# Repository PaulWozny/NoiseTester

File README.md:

## Noise tester for voltage regulators

Borad and software required for tester of noise in power supplies.

This project created to show to show progress in my engineering thesis:

- PL: "Celem pracy jest opracowanie i zbudowanie niskoszumnego układu pozwalającego na pomiar szumów własnych liniowych stabilizatorów napięcia w paśmie do 1 MHz."
- EN: "The goal is to create low noise device which will allow mesure noise of the linear regulatores up to 1MHz"

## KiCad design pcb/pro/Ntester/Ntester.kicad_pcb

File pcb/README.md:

# NoiseTester
Borad and software required for tester of noise in power supplies.

This project created to show to show progress in my engineering thesis:

- PL: "Celem pracy jest opracowanie i zbudowanie niskoszumnego układu pozwalającego na pomiar szumów własnych liniowych stabilizatorów napięcia w paśmie do 1 MHz."
- EN: "The goal is to create low noise device which will allow mesure noise of the linear regulatores up to 1MHz"

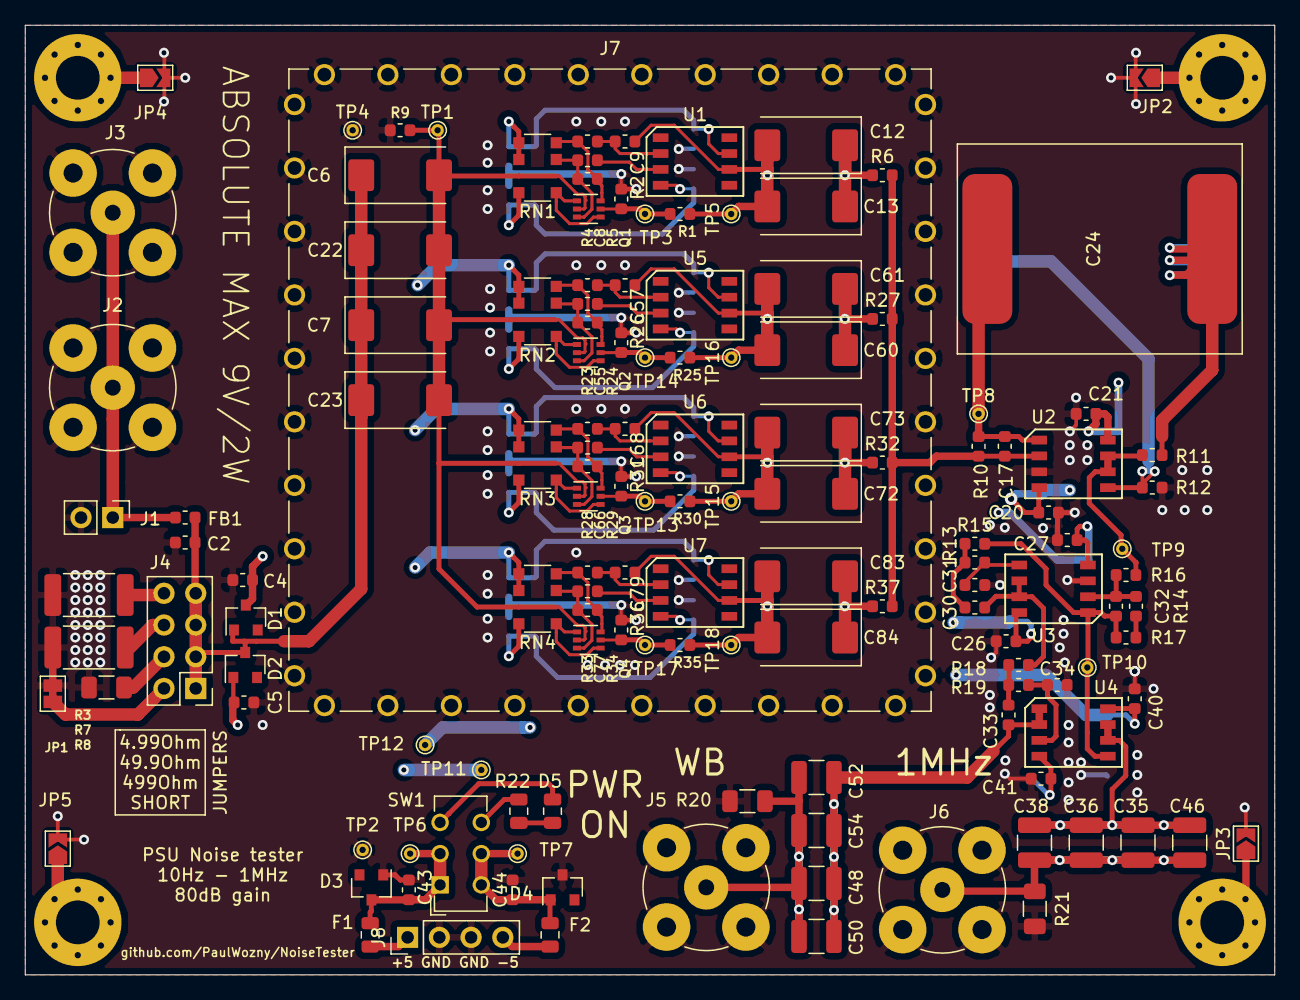
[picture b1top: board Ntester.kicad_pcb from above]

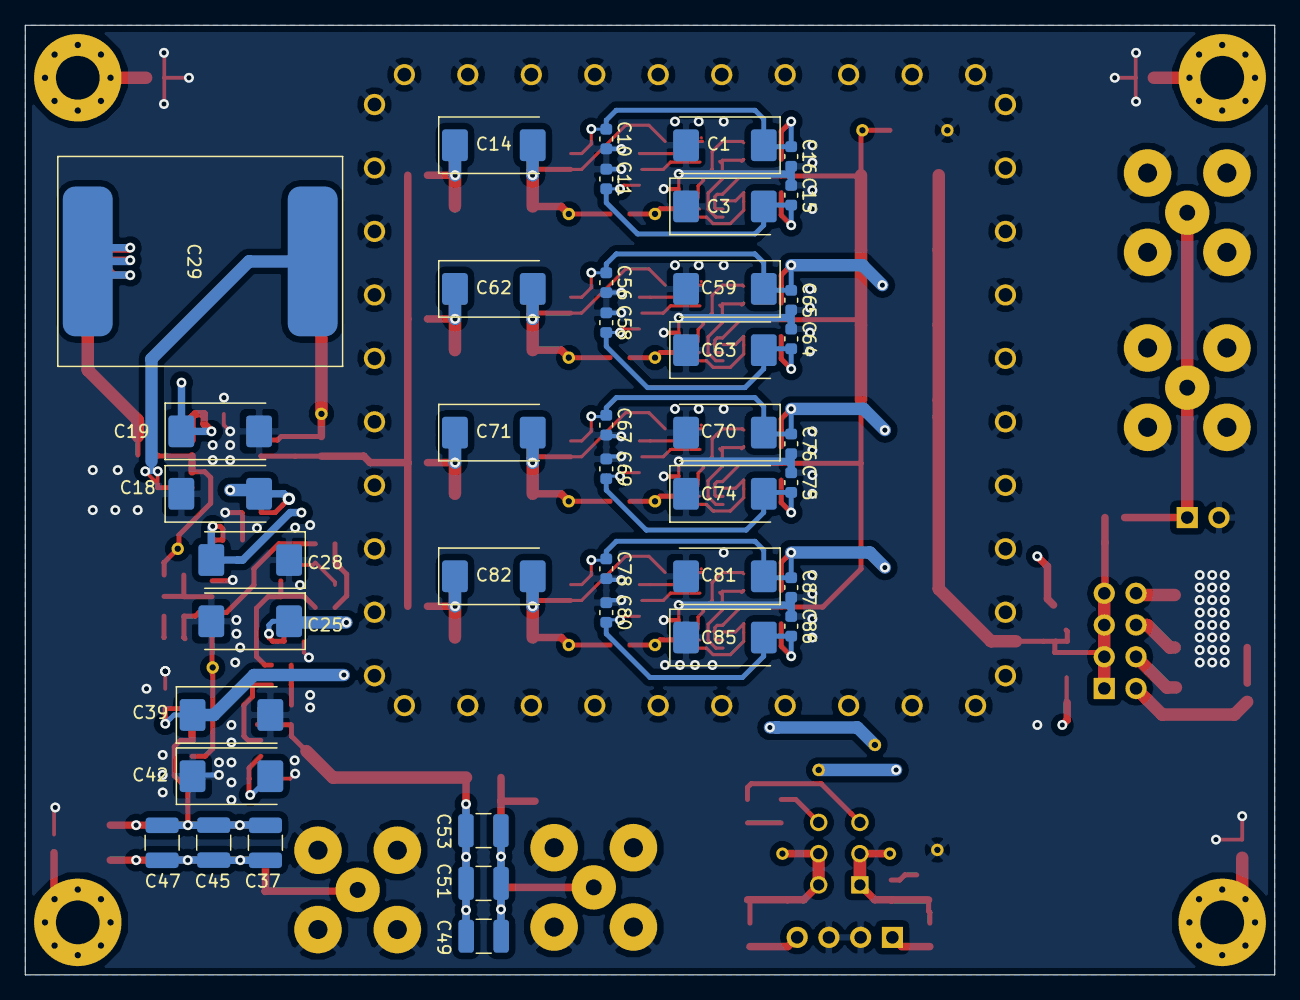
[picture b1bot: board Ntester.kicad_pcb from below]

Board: 4 copper layers, 100.0 x 76.0 mm, 183 parts (41 on the bottom side), 68 nets.

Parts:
C1, C3, C6, C7, C12, C13, C18, C19, C22, C25, C28, C39, C42, C59, C61, C62, C63, C70, C72, C73, C74, C81, C83, C84, C85: B45196-H2227-M409; CP_EIA-7343-31_Kemet-D
C2, C9, C43, C44, C57, C68, C79: 885012006007; R_0603_1608Metric
C4, C5, C10, C11, C15, C16, C20, C21, C26, C27, C40, C41, C56, C58, C64, C65, C67, C69, C75, C76, C78, C80, C86, C87: 0603B104M500CT; R_0603_1608Metric
C8, C55, C66, C77: 885012006038; R_0603_1608Metric
C14, C23, C60, C71, C82: DNP; CP_EIA-7343-31_Kemet-D
C17, C32: DNP; C_0603_1608Metric
C24, C29: SMDTD04470YA00MT00; CAP-6054-SMDTD04470YA00MT00
C30, C31, C33, C34: C_Small; C_0603_1608Metric
C35, C36, C37, C38, C45, C46, C47, C48, C49, C50, C51, C52, C53, C54: GRM32ER60J107ME20K; C_1210_3225Metric
D1, D2, D3, D4: BAS116LT1G; SOT-23
D5: LED_Small; R_0805_2012Metric
F1, F2: Polyfuse_Small; R_0805_2012Metric
FB1: 742792651; R_0603_1608Metric
H1, H2, H3, H4: M3.5; MountingHole_3.5mm_Pad_Via
J1: Conn_01x02_Male; PinHeader_1x02_P2.54mm_Vertical
J2, J3, J5, J6: 5-1634503-1; BNC_TEConnectivity_1478204_Vertical
J4: 67996-408HLF; PinHeader_2x04_P2.54mm_Vertical
J7: 36503505S 36003500S; Wuerth_36503505_50x50mm
J8: PWR IN; PinHeader_1x04_P2.54mm_Vertical
JP1: CAL_FUSE; SolderJumper-2_P1.3mm_Bridged_Pad1.0x1.5mm
JP2, JP3, JP4, JP5: GND_SHIELD; SolderJumper-2_P1.3mm_Open_TrianglePad1.0x1.5mm
Q1, Q2, Q3, Q4: BC847BDW1T1G; SOT-363_SC-70-6
R1, R25, R30, R35: RNCF0603TKY250R; R_0603_1608Metric
R2, R26, R31, R36: RNCF0603AKT10R0; R_0603_1608Metric
R3: RHC2512FT4R99; R_2512_6332Metric
R4, R5, R23, R24, R28, R29, R33, R34: CR0603-JW-471ELF; R_0603_1608Metric
R6, R27, R32, R37: RG1608N-101-W-T1; R_0603_1608Metric
R7: CRM2512-JW-470ELF; R_2512_6332Metric
R8: CR1206-FX-4990ELF; R_1206_3216Metric
R9, R10: RMCF0603FT499R; R_0603_1608Metric
R11, R12, R13, R14, R15, R16, R17, R18, R19: R_Small; R_0603_1608Metric
R20, R21: R_Small; R_1206_3216Metric
R22: 10k; R_0805_2012Metric
RN1, RN2, RN3, RN4: ACASA1001S1001P1AT; R_Array_Convex_4x1206
SW1: JS202011CQN; SW_CuK_JS202011CQN_DPDT_Straight
TP1, TP2, TP3, TP4, TP5, TP6, TP7, TP8, TP9, TP10, TP11, TP12, TP13, TP14, TP15, TP16, TP17, TP18: TestPoint; TestPoint_THTPad_D1.0mm_Drill0.5mm
U1, U5, U6, U7: LT1818; SOIC-8-LINEAR
U2, U3: LT6231; SOIC-8-LINEAR
U4: LT1364; SOIC-8-LINEAR

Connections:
+5V: C3.1, C4.1, C10.1, C16.1, C19.1, C21.1, C25.1, C26.1, C39.1, C40.1, C56.1, C63.1, C65.1, C67.1, C74.1, C76.1, C78.1, C85.1, C87.1, D1.3, D5.2, RN1.5, RN1.6, RN2.5, RN2.6, RN3.5, RN3.6, RN4.5, RN4.6, SW1.3, TP12.1, U1.7, U2.8, U3.8, U4.8, U5.7, U6.7, U7.7
-5V: C1.2, C5.1, C11.2, C15.2, C18.2, C20.1, C27.1, C28.2, C41.1, C42.2, C58.2, C59.2, C64.2, C69.2, C70.2, C75.2, C80.2, C81.2, C86.2, D2.1, R22.2, RN1.8, RN2.8, RN3.8, RN4.8, SW1.6, TP11.1, U1.4, U2.4, U3.4, U4.4, U5.4, U6.4, U7.4
/GainBlock/1MHZ_OUT: C35.1, C36.1, C37.1, C38.1, C45.1, C46.1, C47.1, J6.1, R21.1
/GainBlock/GB_IN: C17.2, R6.1, R10.1, R27.1, R32.1, R37.1, U2.2
/GainBlock/WB_OUT: C48.1, C49.1, C50.1, C51.1, C52.1, C53.1, C54.1, J5.1, R20.1
/InputAmplifier/IN_AMP: C6.2, C7.2, C22.2, C23.2, Q1.2, Q2.2, Q3.2, Q4.2, R9.1, TP1.1
/InputAmplifier/R_LTP0: C8.2, Q1.6, R4.2, RN1.4
/InputAmplifier/R_LTP2: C8.1, Q1.3, R5.2, RN1.3
/InputAmplifier/R_LTP5: Q1.1, Q1.4, RN1.1
/InputStage/IN_STG: FB1.2, J1.1, J2.1, J3.1
/LNA1/R_LTP0: C55.2, Q2.6, R23.2, RN2.4
/LNA1/R_LTP2: C55.1, Q2.3, R24.2, RN2.3
/LNA1/R_LTP5: Q2.1, Q2.4, RN2.1
/LNA2/R_LTP0: C66.2, Q3.6, R28.2, RN3.4
/LNA2/R_LTP2: C66.1, Q3.3, R29.2, RN3.3
/LNA2/R_LTP5: Q3.1, Q3.4, RN3.1
/LNA3/R_LTP0: C77.2, Q4.6, R33.2, RN4.4
/LNA3/R_LTP2: C77.1, Q4.3, R34.2, RN4.3
/LNA3/R_LTP5: Q4.1, Q4.4, RN4.1
GND: C1.1, C2.2, C3.2, C4.2, C5.2, C10.2, C11.1, C15.1, C16.2, C18.1, C19.2, C20.2, C21.2, C25.2, C26.2, C27.2, C28.1, C31.2, C34.2, C39.2, C40.2, C41.2, C42.1, C43.2, C44.2, C56.2, C58.1, C59.1, C63.2, C64.1, C65.2, C67.2, C69.1, C70.1, C74.2, C75.1, C76.2, C78.2, C80.1, C81.1, C85.2, C86.1, C87.2, D3.1, D4.3, J1.2, J2.2, J3.2, J5.2, J6.2, J7.1, J8.2, J8.3, JP1.2, JP2.2, JP3.2, JP4.2, JP5.2, R2.1, R3.2, R7.2, R8.2, R9.2, R12.1, R20.2, R21.2, R26.1, R31.1, R36.1, TP2.1, TP4.1, U2.3, U3.3
unnamed: C2.1, C6.1, C7.1, C22.1, C23.1, D1.1, D2.3, FB1.1, J4.1, J4.3, J4.5, J4.7
unnamed: C9.2, R4.1, U1.2
unnamed: C12.1, C13.1, C14.1, R6.2
unnamed: C9.1, C12.2, C13.2, C14.2, R1.2, TP5.1, U1.6
unnamed: C17.1, C24.2, R10.2, TP8.1, U2.1
unnamed: C24.1, C29.2, R11.1
unnamed: C29.1, R12.2, U2.5
unnamed: C30.1, R18.1, U3.6, U3.7
unnamed: C30.2, R13.2, R15.1
unnamed: C31.1, R15.2, U3.5
unnamed: C32.1, R13.1, R17.1, TP10.1, U3.1, U4.5
unnamed: C32.2, R14.2, R16.1, U3.2
unnamed: C33.1, C48.2, C49.2, C50.2, C51.2, C52.2, C53.2, C54.2, U4.1, U4.2
unnamed: C33.2, R18.2, R19.1
unnamed: C34.1, R19.2, U4.3
unnamed: C35.2, C36.2, C37.2, C38.2, C45.2, C46.2, C47.2, U4.6, U4.7
unnamed: C43.1, D3.3, F1.1, SW1.1, SW1.2, TP6.1
unnamed: C44.1, D4.1, F2.1, SW1.4, SW1.5, TP7.1
unnamed: C57.1, C60.2, C61.2, C62.2, R25.2, TP16.1, U5.6
unnamed: C57.2, R23.1, U5.2
unnamed: C60.1, C61.1, C62.1, R27.2
unnamed: C68.1, C71.2, C72.2, C73.2, R30.2, TP15.1, U6.6
unnamed: C68.2, R28.1, U6.2
unnamed: C71.1, C72.1, C73.1, R32.2
unnamed: C79.1, C82.2, C83.2, C84.2, R35.2, TP18.1, U7.6
unnamed: C79.2, R33.1, U7.2
unnamed: C82.1, C83.1, C84.1, R37.2
unnamed: D5.1, R22.1
unnamed: F1.2, J8.1
unnamed: F2.2, J8.4
unnamed: H1.1, JP2.1
unnamed: H2.1, JP3.1
unnamed: H3.1, JP4.1
unnamed: H4.1, JP5.1
unnamed: J4.2, JP1.1
unnamed: J4.4, R8.1
unnamed: J4.6, R7.1
unnamed: J4.8, R3.1
unnamed: Q1.5, R1.1, R2.2, TP3.1
unnamed: Q2.5, R25.1, R26.2, TP14.1
unnamed: Q3.5, R30.1, R31.2, TP13.1
unnamed: Q4.5, R35.1, R36.2, TP17.1
unnamed: R5.1, U1.3
unnamed: R11.2, R16.2, TP9.1, U2.6, U2.7
unnamed: R14.1, R17.2
unnamed: R24.1, U5.3
unnamed: R29.1, U6.3
unnamed: R34.1, U7.3

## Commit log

2018-10-14 initail commit
2018-10-14 first try
2018-10-19 added basic schematic
2018-10-29 added rest of files
2018-11-01 " alomost" finalized layout
2018-11-02 layout finalized
2018-11-07 BOM was updated
2018-11-14 changed BOM
2018-11-27 Cleanup and update of repo
